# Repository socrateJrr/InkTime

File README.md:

# InkTime Smartwatch — PCB Design

InkTime este un smartwatch open-source si low-cost, cu ecran e-paper.

## Diagrama bloc

## BOM (Bill of Materials)

| Referinta    | Componenta               | Descriere                        | JLC Parts                                                                    | Datasheet                                                                                                   |
| ------------ | ------------------------ | -------------------------------- | ---------------------------------------------------------------------------- | ----------------------------------------------------------------------------------------------------------- |
| U1           | nRF52840-QIAA            | MCU principal BLE 5.0            | [JLC](https://jlcpcb.com/parts/componentSearch?searchTxt=nRF52840)           | [Datasheet](https://infocenter.nordicsemi.com/pdf/nRF52840_PS_v1.7.pdf)                                     |
| IC9          | RT6160AWSC               | DC/DC Buck-Boost 3.3V            | [JLC](https://jlcpcb.com/parts/componentSearch?searchTxt=RT6160AWSC)         | [Datasheet](https://www.richtek.com/assets/product_file/RT6160A/DS6160A-00.pdf)                             |
| IC1          | BQ25180YBGR              | LiPo Charger                     | [JLC](https://jlcpcb.com/parts/componentSearch?searchTxt=BQ25180)            | [Datasheet](https://www.ti.com/lit/ds/symlink/bq25180.pdf)                                                  |
| U3           | MAX17048G+T10            | Fuel Gauge I2C                   | [JLC](https://jlcpcb.com/parts/componentSearch?searchTxt=MAX17048G)          | [Datasheet](https://datasheets.maximintegrated.com/en/ds/MAX17048-MAX17049.pdf)                             |
| IC3          | BMA421                   | IMU Accelerometru 3 axe          | [JLC](https://jlcpcb.com/parts/componentSearch?searchTxt=BMA421)             | [Datasheet](https://www.bosch-sensortec.com/media/boschsensortec/downloads/datasheets/bst-bma421-ds000.pdf) |
| IC2          | DRV2605YZFR              | Haptic Driver I2C                | [JLC](https://jlcpcb.com/parts/componentSearch?searchTxt=DRV2605)            | [Datasheet](https://www.ti.com/lit/ds/symlink/drv2605.pdf)                                                  |
| ANT1         | 2450AT18B100E            | Antena Bluetooth 2.4GHz          | [JLC](https://jlcpcb.com/parts/componentSearch?searchTxt=2450AT18B100E)      | [Datasheet](https://www.johansontechnology.com/datasheets/2450AT18B100E/2450AT18B100E.pdf)                  |
| J1           | 503480-2400              | Conector display e-paper 24 pini | [JLC](https://jlcpcb.com/parts/componentSearch?searchTxt=503480-2400)        | [Datasheet](https://www.molex.com/pdm_docs/sd/5034802400_sd.pdf)                                            |
| J4           | KH-TYPE-C-16P            | Conector USB-C 16 pini           | [JLC](https://jlcpcb.com/parts/componentSearch?searchTxt=KH-TYPE-C-16P)      | -                                                                                                           |
| D3           | USBLC6-2SC6Y             | Protectie ESD USB                | [JLC](https://jlcpcb.com/parts/componentSearch?searchTxt=USBLC6-2SC6Y)       | [Datasheet](https://www.st.com/resource/en/datasheet/usblc6-2.pdf)                                          |
| D2, D4, D5   | MBR0530                  | Dioda Schottky                   | [JLC](https://jlcpcb.com/parts/componentSearch?searchTxt=MBR0530)            | [Datasheet](https://www.onsemi.com/pdf/datasheet/mbr0530-d.pdf)                                             |
| J2           | TC2030-IDC               | Conector SWD Tag-Connect         | [JLC](https://jlcpcb.com/parts/componentSearch?searchTxt=TC2030)             | [Datasheet](https://www.tag-connect.com/wp-content/uploads/bsk-pdf-manager/TC2030-IDC_1.pdf)                |
| X1           | Crystal 32MHz            | Cristal principal MCU            | [JLC](https://jlcpcb.com/parts/componentSearch?searchTxt=32MHz+crystal+3225) | -                                                                                                           |
| X2           | Crystal 32.768kHz        | Cristal RTC                      | [JLC](https://jlcpcb.com/parts/componentSearch?searchTxt=32768+crystal)      | -                                                                                                           |
| L7           | FTC252012SR47MBCA        | Inductor 0.47uH DC/DC            | [JLC](https://jlcpcb.com/parts/componentSearch?searchTxt=FTC252012SR47)      | -                                                                                                           |
| L5           | Inductor 68uH            | Inductor e-paper drive           | [JLC](https://jlcpcb.com/parts/componentSearch?searchTxt=68uH+inductor)      | -                                                                                                           |
| L1           | Inductor 3.9nH           | Inductor RF matching             | [JLC](https://jlcpcb.com/parts/componentSearch?searchTxt=3.9nH+inductor)     | -                                                                                                           |
| L2           | Inductor 15nH            | Inductor RF                      | [JLC](https://jlcpcb.com/parts/componentSearch?searchTxt=15nH+inductor)      | -                                                                                                           |
| L3           | Inductor 10uH            | Inductor DC/DC                   | [JLC](https://jlcpcb.com/parts/componentSearch?searchTxt=10uH+inductor+0402) | -                                                                                                           |
| Q1           | DMG2305UX-7              | MOSFET P-channel e-paper         | [JLC](https://jlcpcb.com/parts/componentSearch?searchTxt=DMG2305UX)          | [Datasheet](https://www.diodes.com/assets/Datasheets/DMG2305UX.pdf)                                         |
| Q3           | SI1308EDL-T1-GE3         | MOSFET N-channel e-paper         | [JLC](https://jlcpcb.com/parts/componentSearch?searchTxt=SI1308EDL)          | [Datasheet](https://www.vishay.com/docs/71509/si1308edl.pdf)                                                |
| SW_UP/DN/ENT | Butoane tactile SMD      | 3 butoane fizice                 | [JLC](https://jlcpcb.com/parts/componentSearch?searchTxt=tactile+button+smd) | -                                                                                                           |
| R*, C*       | Rezistente/Condensatoare | Diverse valori pasive            | [JLC](https://jlcpcb.com/parts)                                              | -                                                                                                           |

---

## Descrierea functionalitatii hardware

### Microcontroller — nRF52840 (U1)

Nucleul dispozitivului este **nRF52840** de la Nordic Semiconductor, un SoC cu procesor ARM Cortex-M4 la 64MHz si BLE 5.0 integrat. Acesta coordoneaza toate perifericele prin interfetele SPI, I2C si GPIO.

Antena externa **ANT1** (2450AT18B100E) este o antena ceramica de 2.4GHz plasata la marginea dreapta a placii. Sub antena exista un decupaj in PCB pentru a maximiza performanta RF — FR4-ul absoarbe semnalul daca antena sta direct pe el. Circuitul de adaptare RF include inductorii L1 (3.9nH), L2 (15nH) si condensatoarele C3, C4, C22.

**Interfete folosite:**

- **SPI** → display e-paper (J1): MOSI, SCK, CS, DC, RST, BUSY
- **I2C** → IMU (IC3), charger (IC1), haptic (IC2), fuel gauge (U3), DC/DC (IC9)
- **USB** → D+/D- prin protectie ESD D3
- **SWD** → programare/debug prin J2 (TC2030-IDC)
- **GPIO** → butoane, intreruperi IMU, HAPTIC_EN

### Alimentare

**IC1 (BQ25180YBGR)** — charger LiPo care preia alimentarea de la USB-C si incarca bateria. Comunica cu MCU prin I2C pentru statusul incarcarii.

**IC9 (RT6160AWSC)** — DC/DC buck-boost converter care genereaza **3.3V stabil** din tensiunea bateriei (3V–4.2V). Inductorul L7 (0.47uH) face parte din circuitul de comutare. Condensatoarele C23, C24 filtreaza intrarea si C25, C33 iesirea.

**U3 (MAX17048G+T10)** — fuel gauge care monitorizeaza nivelul bateriei prin I2C si trimite o intrerupere (ALERT) la nRF cand bateria scade sub un prag configurat.

Bateria se conecteaza direct la test pad-urile **TP_VBAT** si **TP_BAT_GND** (fara conector JST) pentru economisire de spatiu.

### Display e-paper — J1 (503480-2400)

Conector FFC ZIF cu 24 de pini. Circuitul de drive include Q3, Q1, L5 (68uH), D2, D4, D5 si condensatoarele EPD_C1...C12. Comunicatie prin **SPI** + GPIO de control.

### IMU — BMA421 (IC3)

Accelerometru triaxial Bosch conectat prin **I2C**. Folosit pentru wake-on-wrist, pedometru si detectie orientare. Intreruperile IMU_INT1/INT2 sunt conectate la GPIO-uri dedicate ale nRF.

### Haptic — DRV2605YZFR (IC2)

Driver de motor haptic controlat prin **I2C**, activat prin **HAPTIC_EN**. Suporta efecte LRA si ERM din biblioteca interna de 123 efecte.

### USB-C — KH-TYPE-C-16P (J4)

Conector USB-C cu protectie ESD asigurata de D3 (USBLC6-2SC6Y). R1_USB si R2_USB (5K1) pe pinii CC1/CC2 pentru detectia cablului USB.

### Programare SWD — TC2030-IDC (J2)

Conector Tag-Connect 6 pini pentru programare si debug SWD. Semnale: SWDIO, SWDCLK, RESET, SWO, 3.3V, GND.

---

## Pinii nRF52840 folositi

| Pin nRF52840  | Semnal    | Componenta             | Functie                       |
| ------------- | --------- | ---------------------- | ----------------------------- |
| P0.00 (XL1)   | XL1       | X1 (32MHz)             | Cristal principal — clock MCU |
| P0.01 (XL2)   | XL2       | X1 (32MHz)             | Cristal principal — clock MCU |
| P0.26         | SCL       | IC3, IC1, IC2, U3, IC9 | I2C clock                     |
| P0.27         | SDA       | IC3, IC1, IC2, U3, IC9 | I2C data                      |
| P0.13         | D-        | J4 via D3              | USB Data minus                |
| P0.14         | D+        | J4 via D3              | USB Data plus                 |
| P0.17         | EPD_RST   | J1                     | Reset display e-paper         |
| P0.18 (RESET) | RESET     | J2                     | Reset MCU via SWD             |
| P0.19         | EPD_BUSY  | J1                     | Status display e-paper        |
| P0.20         | EPD_DC    | J1                     | Data/Command display          |
| P0.21         | EPD_CS    | J1                     | Chip select display SPI       |
| P0.22         | SCK       | J1                     | SPI clock display             |
| P0.23         | MOSI      | J1                     | SPI data display              |
| P0.24         | SWDCLK    | J2                     | SWD clock programare          |
| P0.25         | SWDIO     | J2                     | SWD data programare           |
| P1.01         | HAPTIC_EN | IC2                    | Enable haptic driver          |
| P1.02         | PMIC_INT  | IC1                    | Intrerupere charger           |
| P1.03         | IMU_INT1  | IC3                    | Intrerupere IMU 1             |
| P1.04         | IMU_INT2  | IC3                    | Intrerupere IMU 2             |
| P1.05         | SW_UP     | SW_UP                  | Buton sus                     |
| P1.06         | SW_ENT    | SW_ENT                 | Buton enter                   |
| P1.07         | SW_DN     | SW_DN                  | Buton jos                     |
| ANT           | RF        | ANT1                   | Antena Bluetooth 2.4GHz       |
| VBUS          | VBUS      | J4                     | Detectie USB conectat         |
| DEC3V3        | 3V3       | IC9 output             | Alimentare 3.3V               |

---

## Structura PCB

**Dimensiuni:** 46mm x 35mm, grosime 1mm
**Straturi:** 4 (Top + GND + Power + Bottom)

| Strat            | Continut                        | Latime trasee |
| ---------------- | ------------------------------- | ------------- |
| Top              | Componente SMD + semnale date   | min 0.15mm    |
| GND (interior)   | Plan de masa complet            | -             |
| Power (interior) | Trasee 3V3, VBAT, VBUS, VREG    | 0.3mm         |
| Bottom           | Semnale suplimentare + plan GND | min 0.15mm    |

Toate componentele sunt plasate exclusiv pe stratul **TOP**.

---

## Decizii de design

**Alegerea 4 straturi**
S-a optat pentru 4 straturi datorita densitatii mari de componente si numarului mare de semnale. Stratul interior Power permite rutarea traseelor de alimentare (3V3, VBAT, VBUS) separat de semnale.

**Conectarea GND prin Copper Pour**
Pinii de GND nu au fost conectati manual prin trasee individuale.
In schimb, s-au realizat planuri de masa (copper pour GND) pe straturile
Top, GND interior si Bottom. Prin refill-ul poligoanelor, toate padurile
de GND se conecteaza automat la planul de cupru, eliminand necesitatea
airwires-urilor individuale de GND.

## Erori DRC acceptate

- **Board Outline Clearance (~40 erori)** — cauzate de plasarea butoanelor si mufei USB conform specificatiilor mecanice. Neglijate conform enuntului proiectului.
- **"Only INPUT pins on NET ID"** — ignorata conform indicatiilor din enunt.
- **Erori de Dimension la butoane si USB** — neglijate conform enuntului.
- **Overlap-uri** — in anumite zone foarte aglomerate ale PCB-ului, rutarea semnalelor nu a putut evita complet apropierea de pinii vecini fara a intrerupe conexiunile necesare. S-a acceptat un numar mic de overlap-uri in aceste zone.
- **Fisierul `.fbrd` de referinta furnizat continea deja ~46 de erori DRC** din cauza formei si constructiei componentelor. Acestea nu au putut fi eliminate deoarece tin de geometria placii impuse.

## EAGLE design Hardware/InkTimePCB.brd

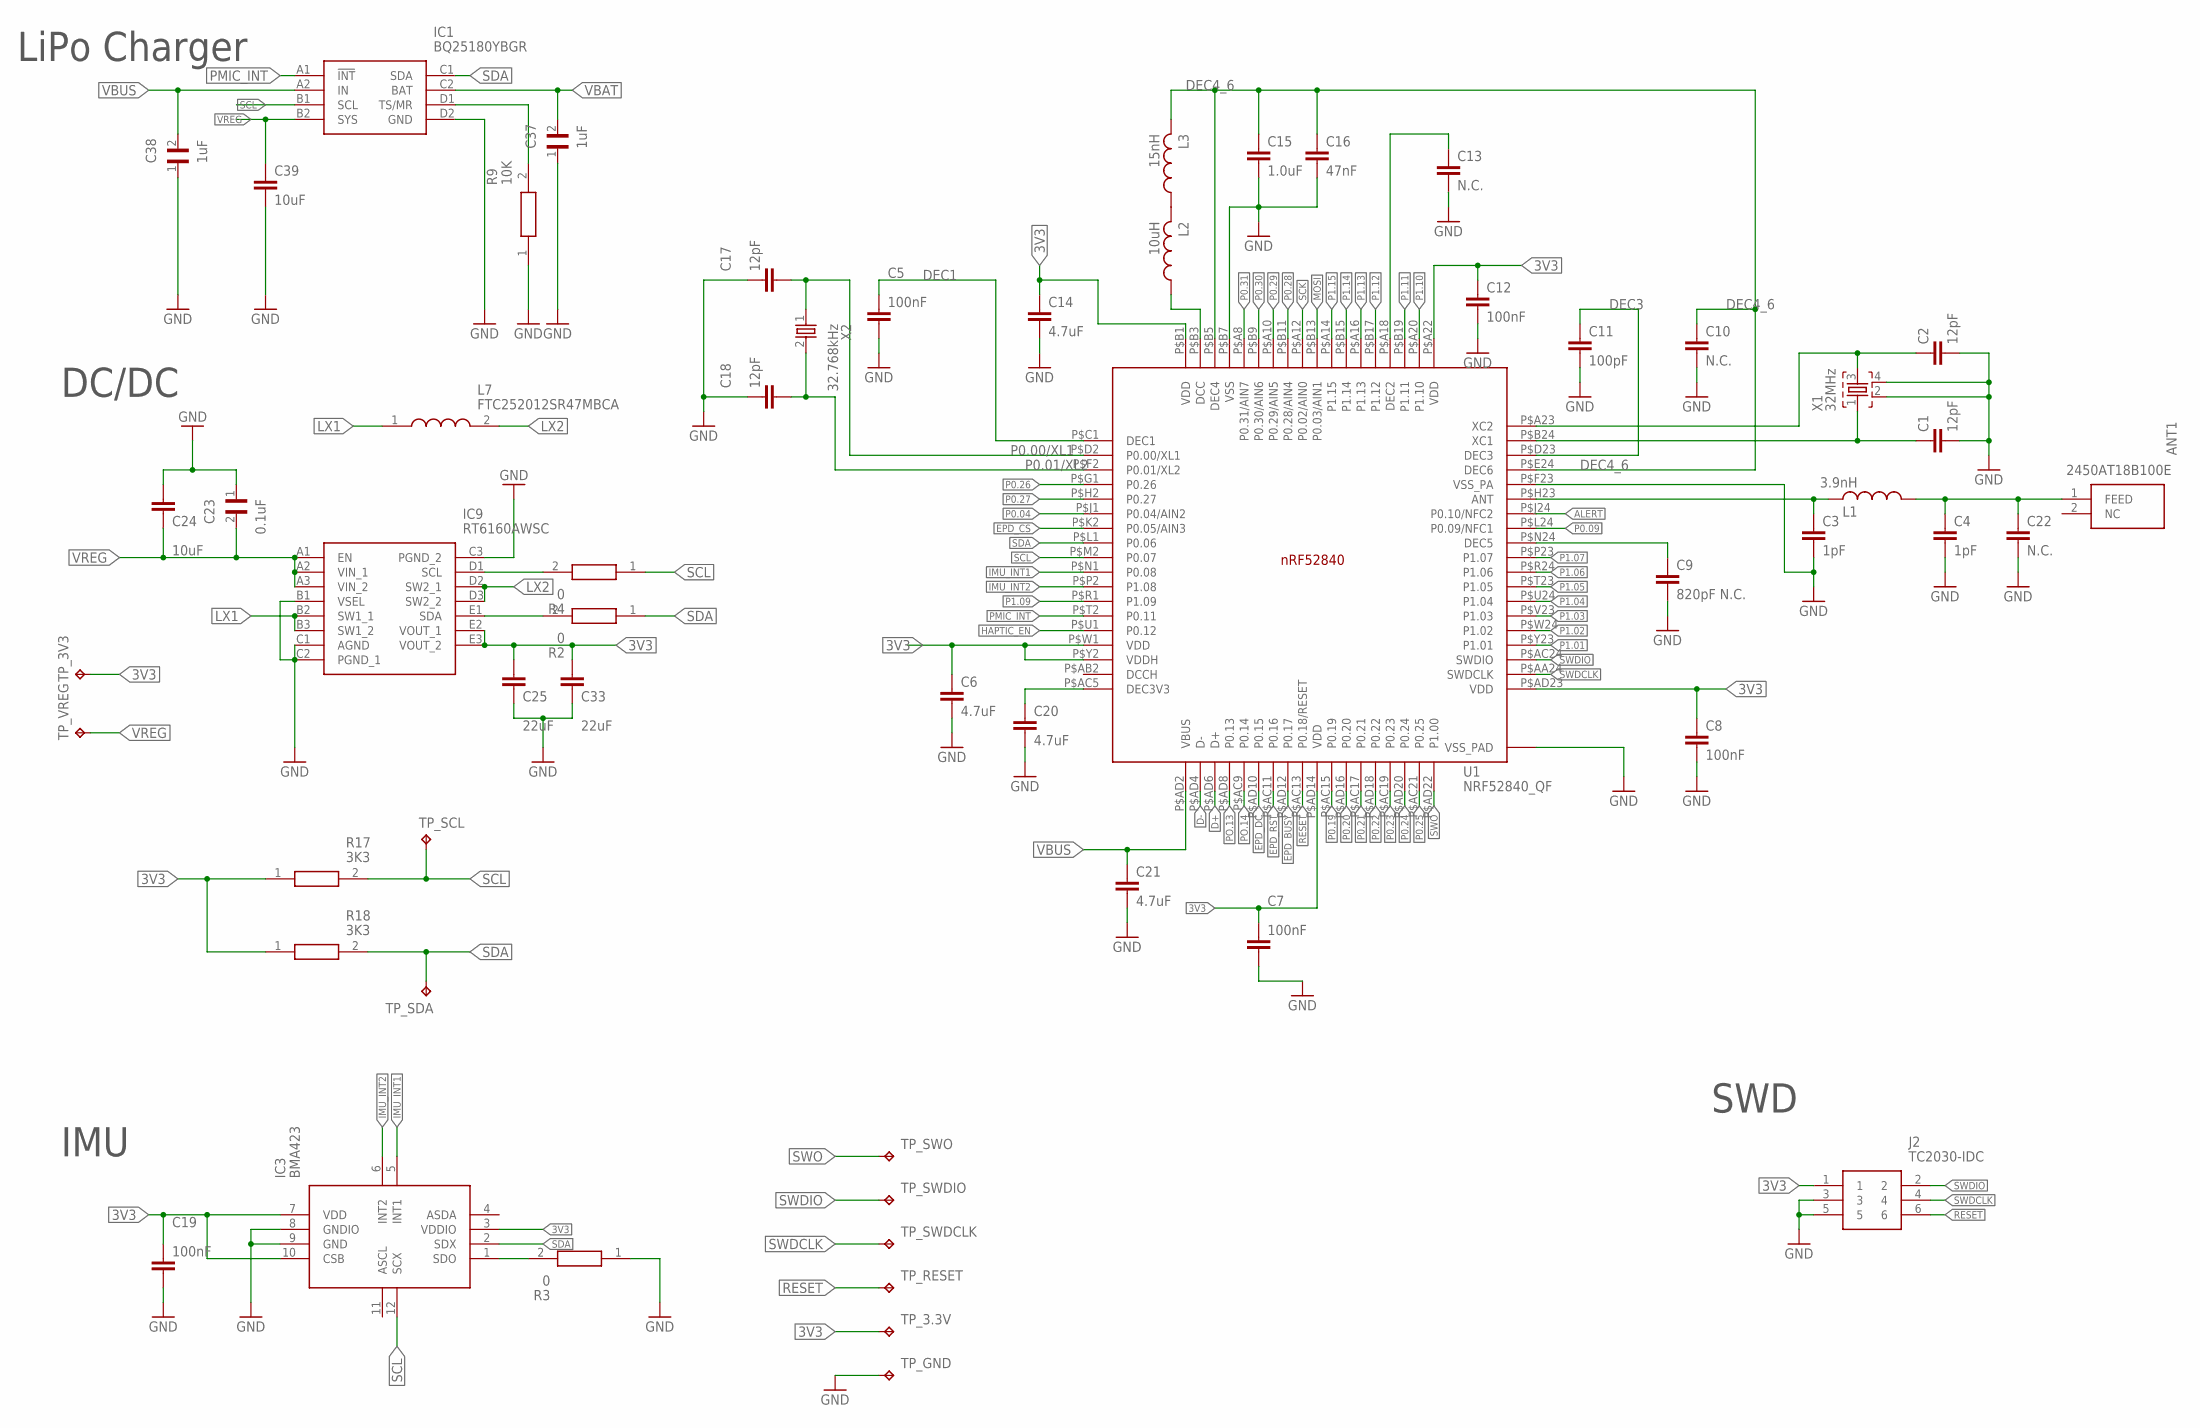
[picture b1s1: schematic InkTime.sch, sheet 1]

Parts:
ANT1: 2450AT18B100E; 2450AT18B100E_ANTC3216X140N
C1, C2, C17, C18: 12pF; NORDIC_NRF_3_RESC0201_L
C3, C4: 1pF; NORDIC_NRF_3_RESC0201_L
C5, C7, C8, C12, C19: 100nF; NORDIC_NRF_3_RESC0201_L
C6, C14, C20, C21: 4.7uF; PERFECT_0402_0402
C9: 820pF N.C.; NORDIC_NRF_3_RESC0201_L
C10, C13, C22: N.C.; NORDIC_NRF_3_RESC0201_L
C11: 100pF; NORDIC_NRF_3_RESC0201_L
C15: 1.0uF; PERFECT_0402_0402
C16: 47nF; NORDIC_NRF_3_RESC0201_L
C23: 0.1uF; GRM011R60J152KE01L_1_0201
C24: 10uF; PERFECT_0402_0402
C25, C33: 22uF; PERFECT_0402_0402
C37, C38: 1uF; GRM011R60J152KE01L_1_0201
C39: 10uF; ESP32_C6_LIBRARY_1_ESP32_WROVER_EAGLE-LTSPICE_C0402
IC1: BQ25180YBGR; BQ25180YBGR_BGA8C40P2X4_100X155X50
IC3: BMA423; BMA423_BMA423
IC9: RT6160AWSC; RT6160AWSC_BGA15C40P3X5_140X230X60
J2: TC2030-IDC; TC2030-IDC_TC2030IDC
L1: 3.9nH; NORDIC_NRF_2_RESC0402_L
L2: 10uH; NORDIC_NRF_2_RESC0402_L
L3: 15nH; NORDIC_NRF_2_RESC0402_L
L7: FTC252012SR47MBCA; MLP2016SR47MT0S1_INDC2016X100N
R2, R4: 0; ERA-1AEB3401C_0201
R3: 0; CPF0201D7K68C1_0201
R9: 10K; ERA-1AEB3401C_0201
R17, R18: 3K3; ERA-1AEB3401C_0201
TP_3.3V, TP_3V3: HECTOR_WATCH_1_TPTP20R; HECTOR_WATCH_1_TP20R
TP_GND: HECTOR_WATCH_1_TPTP20R; HECTOR_WATCH_1_TP20R
TP_RESET: HECTOR_WATCH_1_TPTP20R; HECTOR_WATCH_1_TP20R
TP_SCL: HECTOR_WATCH_1_TPTP20R; HECTOR_WATCH_1_TP20R
TP_SDA: HECTOR_WATCH_1_TPTP20R; HECTOR_WATCH_1_TP20R
TP_SWDCLK: HECTOR_WATCH_1_TPTP20R; HECTOR_WATCH_1_TP20R
TP_SWDIO: HECTOR_WATCH_1_TPTP20R; HECTOR_WATCH_1_TP20R
TP_SWO: HECTOR_WATCH_1_TPTP20R; HECTOR_WATCH_1_TP20R
TP_VREG: HECTOR_WATCH_1_TPTP20R; HECTOR_WATCH_1_TP20R
U1: NRF52840_QF; NORDIC_NRF_4_AQFN50P700X700X85_HS-74N
X1: 32MHz; NORDIC_NRF_BT-XTAL_2016_N
X2: 32.768kHz; NORDIC_NRF_1_XTAL_3215_N

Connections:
3V3: C6.1, C7.1, C8.1, C12.1, C14.1, C19.1, C25.1, C33.1, IC3.3 (VDDIO), IC3.7 (VDD), IC3.10 (CSB), IC9.E2 (VOUT_1), IC9.E3 (VOUT_2), J2.1, R17.1, R18.1, TP_3.3V.TP, TP_3V3.TP, U1.P$A22 (VDD), U1.P$AD14 (VDD), U1.P$AD23 (VDD), U1.P$B1 (VDD), U1.P$W1 (VDD), U1.P$Y2 (VDDH); also elsewhere on the board
ALERT: U1.P$J24 (P0.10/NFC2); also elsewhere on the board
D+: U1.P$AD6 (D+); also elsewhere on the board
D-: U1.P$AD4 (D-); also elsewhere on the board
DEC1: C5.1, U1.P$C1 (DEC1)
DEC3: C11.1, U1.P$D23 (DEC3)
DEC4_6: C10.1, C15.1, C16.1, L3.2, U1.P$B5 (DEC4), U1.P$E24 (DEC6)
EPD_BUSY: U1.P$AD12 (P0.17); also elsewhere on the board
EPD_CS: U1.P$K2 (P0.05/AIN3); also elsewhere on the board
EPD_DC: U1.P$AD10 (P0.15); also elsewhere on the board
EPD_RST: U1.P$AC11 (P0.16); also elsewhere on the board
GND: C1.2, C2.2, C3.2, C4.2, C5.2, C6.2, C7.2, C8.2, C9.2, C10.2, C11.2, C12.2, C13.2, C14.2, C15.2, C16.2, C17.1, C18.1, C19.2, C20.2, C21.2, C22.2, C23.1, C24.1, C25.2, C33.2, C37.1, C38.1, C39.2, IC1.D2 (GND), IC3.8 (GNDIO), IC3.9 (GND), IC9.B1 (VSEL), IC9.C1 (AGND), IC9.C2 (PGND_1), IC9.C3 (PGND_2), J2.3, J2.5, R3.1, R9.1, TP_GND.TP, U1.P$74 (VSS_PAD), U1.P$75 (VSS_PAD), U1.P$76 (VSS_PAD), U1.P$77 (VSS_PAD), U1.P$78 (VSS_PAD), U1.P$79 (VSS_PAD), U1.P$80 (VSS_PAD), U1.P$81 (VSS_PAD), U1.P$82 (VSS_PAD), U1.P$83 (VSS_PAD), U1.P$84 (VSS_PAD), U1.P$85 (VSS_PAD), U1.P$86 (VSS_PAD), U1.P$87 (VSS_PAD), U1.P$88 (VSS_PAD), U1.P$89 (VSS_PAD), U1.P$90 (VSS_PAD), U1.P$B7 (VSS), U1.P$F23 (VSS_PA), X1.2, X1.4; also elsewhere on the board
HAPTIC_EN: U1.P$U1 (P0.12); also elsewhere on the board
IMU_INT1: IC3.5 (INT1), U1.P$N1 (P0.08)
IMU_INT2: IC3.6 (INT2), U1.P$P2 (P1.08)
LX1: IC9.B2 (SW1_1), IC9.B3 (SW1_2), L7.1
LX2: IC9.D2 (SW2_1), IC9.D3 (SW2_2), L7.2
MOSI: U1.P$B13 (P0.03/AIN1); also elsewhere on the board
unnamed: ANT1.1 (FEED), C4.1, C22.1, L1.2
unnamed: IC9.D1 (SCL), R4.2
unnamed: IC1.D1 (TS/MR), R9.2
unnamed: C2.1, U1.P$A23 (XC2), X1.3
unnamed: IC9.E1 (SDA), R2.2
unnamed: L2.2, L3.1
unnamed: IC3.1 (SDO), R3.2
unnamed: C1.1, U1.P$B24 (XC1), X1.1
unnamed: C3.1, L1.1, U1.P$H23 (ANT)
unnamed: C9.1, U1.P$N24 (DEC5)
unnamed: C20.1, U1.P$AC5 (DEC3V3)
unnamed: L2.1, U1.P$B3 (DCC)
unnamed: C13.1, U1.P$A18 (DEC2)
P0.00/XL1: C17.2, U1.P$D2 (P0.00/XL1), X2.1
P0.01/XL2: C18.2, U1.P$F2 (P0.01/XL2), X2.2
P0.04: U1.P$J1 (P0.04/AIN2)
P0.09: U1.P$L24 (P0.09/NFC1)
P0.19: U1.P$AC15 (P0.19)
P0.20: U1.P$AD16 (P0.20)
P0.21: U1.P$AC17 (P0.21)
P0.22: U1.P$AD18 (P0.22)
P0.23: U1.P$AC19 (P0.23)
P0.24: U1.P$AD20 (P0.24)
P0.25: U1.P$AC21 (P0.25)
P0.26: U1.P$G1 (P0.26)
P0.27: U1.P$H2 (P0.27)
P0.28: U1.P$B11 (P0.28/AIN4)
P0.29: U1.P$A10 (P0.29/AIN5)
P0.30: U1.P$B9 (P0.30/AIN6)
P0.31: U1.P$A8 (P0.31/AIN7)
P1.01: U1.P$Y23 (P1.01); also elsewhere on the board
P1.02: U1.P$W24 (P1.02); also elsewhere on the board
P1.03: U1.P$V23 (P1.03)
P1.04: U1.P$U24 (P1.04)
P1.05: U1.P$T23 (P1.05)
P1.06: U1.P$R24 (P1.06)
P1.07: U1.P$P23 (P1.07)
P1.09: U1.P$R1 (P1.09)
P1.10: U1.P$A20 (P1.10)
P1.11: U1.P$B19 (P1.11)
P1.12: U1.P$B17 (P1.12)
P1.13: U1.P$A16 (P1.13)
P1.14: U1.P$B15 (P1.14)
P1.15: U1.P$A14 (P1.15)
PMIC_INT: IC1.A1 (!INT), U1.P$T2 (P0.11)
PO.13: U1.P$AD8 (P0.13)
PO.14: U1.P$AC9 (P0.14)
RESET: J2.6, TP_RESET.TP, U1.P$AC13 (P0.18/RESET)
SCK: U1.P$A12 (P0.02/AIN0); also elsewhere on the board
SCL: IC1.B1 (SCL), IC3.12 (SCX), R4.1, R17.2, TP_SCL.TP, U1.P$M2 (P0.07); also elsewhere on the board
SDA: IC1.C1 (SDA), IC3.2 (SDX), R2.1, R18.2, TP_SDA.TP, U1.P$L1 (P0.06); also elsewhere on the board
SWDCLK: J2.4, TP_SWDCLK.TP, U1.P$AA24 (SWDCLK)
SWDIO: J2.2, TP_SWDIO.TP, U1.P$AC24 (SWDIO)
SWO: TP_SWO.TP, U1.P$AD22 (P1.00)
VBAT: C37.2, IC1.C2 (BAT); also elsewhere on the board
VBUS: C21.1, C38.2, IC1.A2 (IN), U1.P$AD2 (VBUS); also elsewhere on the board
VREG: C23.2, C24.2, C39.1, IC1.B2 (SYS), IC9.A1 (EN), IC9.A2 (VIN_1), IC9.A3 (VIN_2), TP_VREG.TP

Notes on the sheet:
LiPo Charger
DC/DC
IMU
SWD

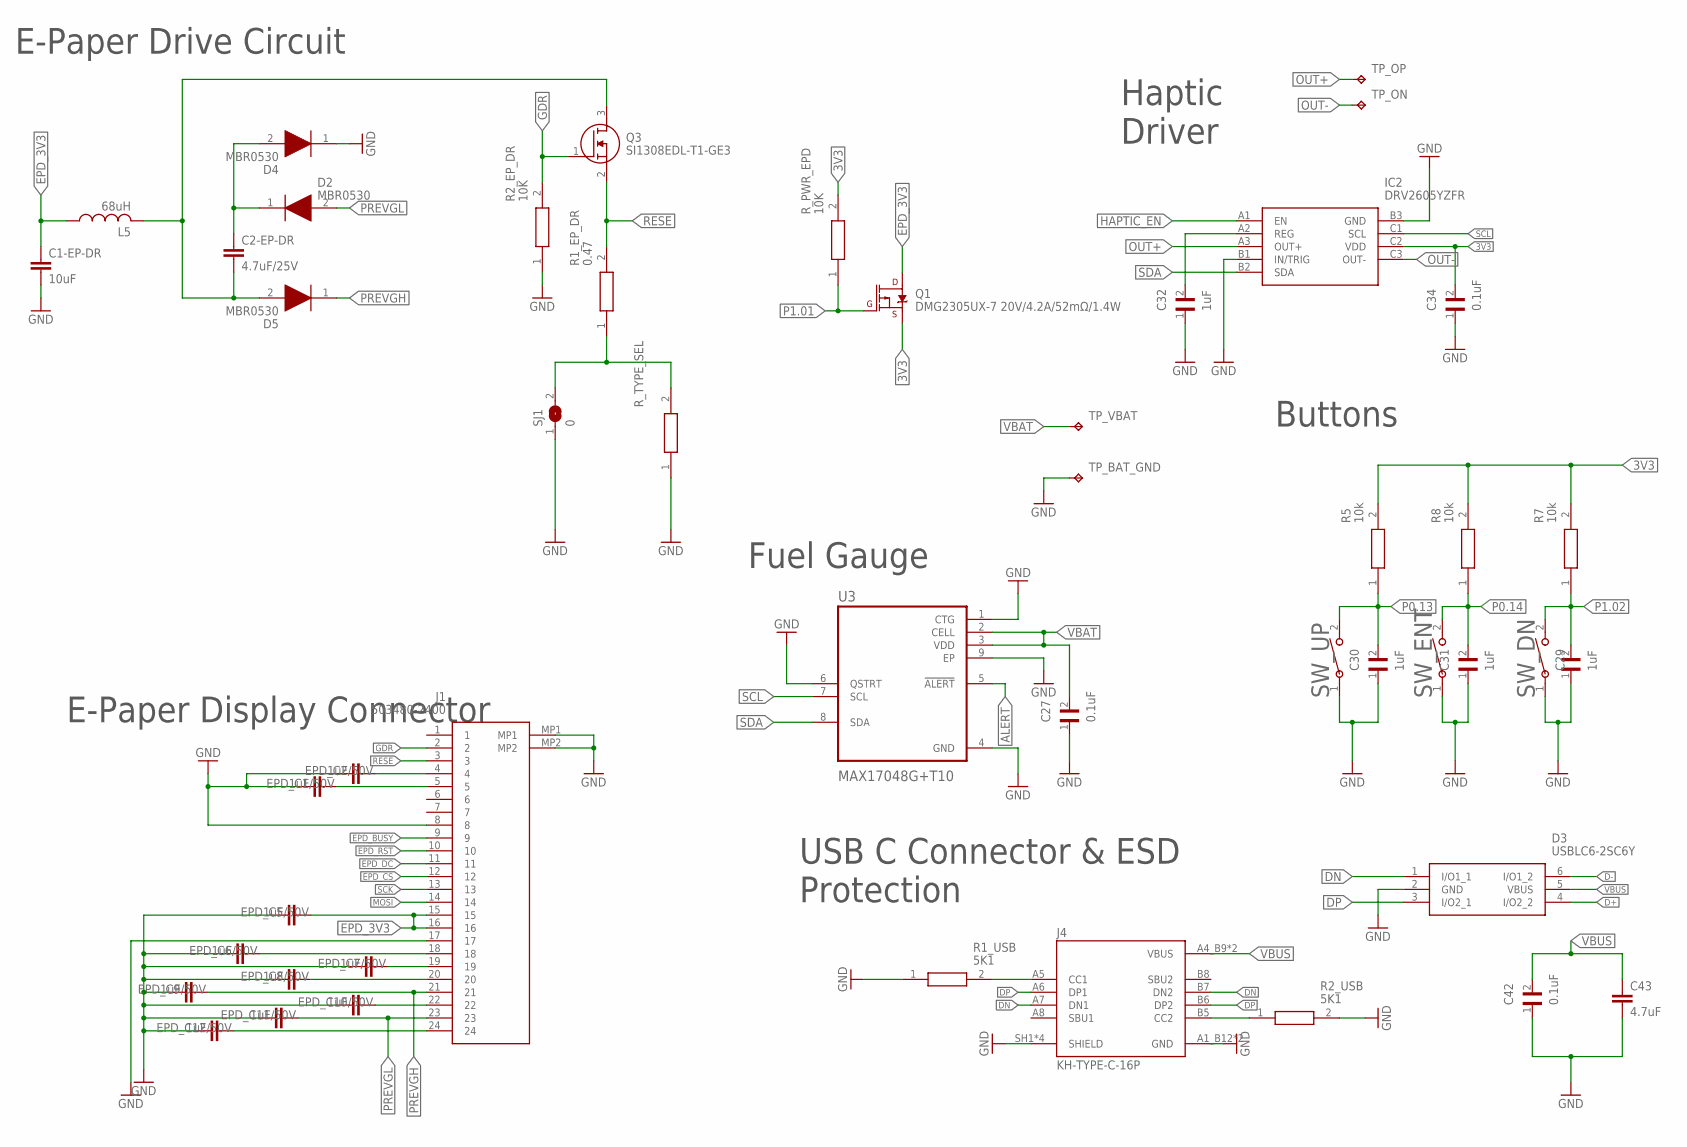
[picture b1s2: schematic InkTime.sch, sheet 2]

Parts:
C1-EP-DR: 10uF; PERFECT_0402_0402
C2-EP-DR: 4.7uF/25V; PERFECT_0402_0402
C27, C34, C42: 0.1uF; GRM011R60J152KE01L_2_CAPC0201X13N
C29, C30, C31, C32: 1uF; GRM011R60J152KE01L_2_CAPC0201X13N
C43: 4.7uF; PERFECT_0402_0402
D2, D4, D5: MBR0530; ESP32_C6_LIBRARY_5_SOD3716X135N
D3: USBLC6-2SC6Y; ESP32_C6_LIBRARY_3_SOT95P280X145-6N
EPD_C1, EPD_C2, EPD_C5, EPD_C6, EPD_C7, EPD_C8, EPD_C9, EPD_C10, EPD_C11, EPD_C12: 1uF/50V; PERFECT_0402_0402
IC2: DRV2605YZFR; DRV2605YZFR_BGA9C50P3X3_144X144X62
J1: 503480-2400; 503480-2400_5034802400
J4: KH-TYPE-C-16P; KH-TYPE-C-16P_KINGHELM_KH-TYPE-C-16P
L5: 68uH; NORDIC_NRF_2_RESC0402_L
Q1: DMG2305UX-7 20V/4.2A/52mΩ/1.4W; ESP32_C6_LIBRARY_4_ESP32_C6_LIBRARY_4_ESP32_C6_LIBRARY_4_ES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
Q3: SI1308EDL-T1-GE3; ESP32_C6_LIBRARY_6_SOT65P210X110-3N
R1_EP_DR: 0.47; ERA-1AEB3401C_0201
R1_USB, R2_USB: 5K1; CPF0201D7K68C1_0201
R2_EP_DR: 10K; ERA-1AEB3401C_0201
R5, R7, R8: 10k; CPF0201D7K68C1_0201
R_PWR_EPD: 10K; CPF0201D7K68C1_0201
R_TYPE_SEL: 2.2; ERA-1AEB3401C_0201
SJ1: 0; ESP32_C6_LIBRARY_7_JUMPER_SJ
SW_DN: 2025-10-22_07-23-44_LIBRARY_EVP-AKE31ASW_EVP-AKE3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; 2025-10-22_07-23-44_LIBRARY_SW_EVP-AKE31A_PAN
SW_ENT: 2025-10-22_07-23-44_LIBRARY_EVP-AKE31ASW_EVP-AKE3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; 2025-10-22_07-23-44_LIBRARY_SW_EVP-AKE31A_PAN
SW_UP: 2025-10-22_07-23-44_LIBRARY_EVP-AKE31ASW_EVP-AKE3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; 2025-10-22_07-23-44_LIBRARY_SW_EVP-AKE31A_PAN
TP_BAT_GND: HECTOR_WATCH_1_TPTP20R; HECTOR_WATCH_1_TP20R
TP_ON: HECTOR_WATCH_1_TPTP20R; HECTOR_WATCH_1_TP20R
TP_OP: HECTOR_WATCH_1_TPTP20R; HECTOR_WATCH_1_TP20R
TP_VBAT: HECTOR_WATCH_1_TPTP20R; HECTOR_WATCH_1_TP20R
U3: MAX17048G+T10; ESP32_C6_LIBRARY_SON50P200X200X80-9N

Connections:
3V3: C34.2, IC2.C2 (VDD), Q1.2 (S), R5.2, R7.2, R8.2, R_PWR_EPD.2; also elsewhere on the board
ALERT: U3.5 (!ALERT); also elsewhere on the board
D+: D3.4 (I/O2_2); also elsewhere on the board
D-: D3.6 (I/O1_2); also elsewhere on the board
DN: D3.1 (I/O1_1), J4.A7 (DN1), J4.B7 (DN2)
DP: D3.3 (I/O2_1), J4.A6 (DP1), J4.B6 (DP2)
EPD_3V3: C1-EP-DR.1, EPD_C5.2, J1.15, J1.16, L5.1, Q1.3 (D)
EPD_BUSY: J1.9; also elsewhere on the board
EPD_CS: J1.12; also elsewhere on the board
EPD_DC: J1.11; also elsewhere on the board
EPD_RST: J1.10; also elsewhere on the board
GDR: J1.2, Q3.1 (G), R2_EP_DR.2
GND: C1-EP-DR.2, C27.1, C29.1, C30.1, C31.1, C32.1, C34.1, C42.1, C43.2, D3.2 (GND), D4.1 (K), EPD_C1.1, EPD_C2.1, EPD_C5.1, EPD_C6.1, EPD_C7.1, EPD_C8.1, EPD_C9.1, EPD_C10.1, EPD_C11.1, EPD_C12.1, IC2.B1 (IN/TRIG), IC2.B3 (GND), J1.8, J1.17, J1.MP1, J1.MP2, J4.A1_B12 (GND), J4.A12_B1 (GND), J4.SH1 (SHIELD), J4.SH2 (SHIELD), J4.SH3 (SHIELD), J4.SH4 (SHIELD), R1_USB.1, R2_EP_DR.1, R2_USB.2, R_TYPE_SEL.1, SJ1.1, SW_DN.1, SW_ENT.1, SW_UP.1, TP_BAT_GND.TP, U3.1 (CTG), U3.4 (GND), U3.6 (QSTRT), U3.9 (EP); also elsewhere on the board
HAPTIC_EN: IC2.A1 (EN); also elsewhere on the board
MOSI: J1.14; also elsewhere on the board
unnamed: J4.A5 (CC1), R1_USB.2
unnamed: C32.2, IC2.A2 (REG)
unnamed: C2-EP-DR.1, D2.1 (K), D4.2 (A)
unnamed: R1_EP_DR.1, R_TYPE_SEL.2, SJ1.2
unnamed: C2-EP-DR.2, D5.2 (A), L5.2, Q3.3 (D)
unnamed: EPD_C2.2, J1.4
unnamed: EPD_C1.2, J1.5
unnamed: J4.B5 (CC2), R2_USB.1
unnamed: EPD_C6.2, J1.18
unnamed: EPD_C7.2, J1.19
unnamed: EPD_C8.2, J1.20
unnamed: EPD_C10.2, J1.22
unnamed: EPD_C12.2, J1.24
OUT+: IC2.A3 (OUT+), TP_OP.TP
OUT-: IC2.C3 (OUT-), TP_ON.TP
P0.13: C30.2, R5.1, SW_UP.2
P0.14: C31.2, R8.1, SW_ENT.2
P1.01: Q1.1 (G), R_PWR_EPD.1; also elsewhere on the board
P1.02: C29.2, R7.1, SW_DN.2; also elsewhere on the board
PREVGH: D5.1 (K), EPD_C9.2, J1.21
PREVGL: D2.2 (A), EPD_C11.2, J1.23
RESE: J1.3, Q3.2 (S), R1_EP_DR.2
SCK: J1.13; also elsewhere on the board
SCL: IC2.C1 (SCL), U3.7 (SCL); also elsewhere on the board
SDA: IC2.B2 (SDA), U3.8 (SDA); also elsewhere on the board
VBAT: C27.2, TP_VBAT.TP, U3.2 (CELL), U3.3 (VDD); also elsewhere on the board
VBUS: C42.2, C43.1, D3.5 (VBUS), J4.A4_B9 (VBUS), J4.A9_B4 (VBUS); also elsewhere on the board

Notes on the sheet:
E-Paper Drive Circuit
E-Paper Display Connector
Fuel Gauge
Haptic Driver
Buttons
USB C Connector & ESD Protection

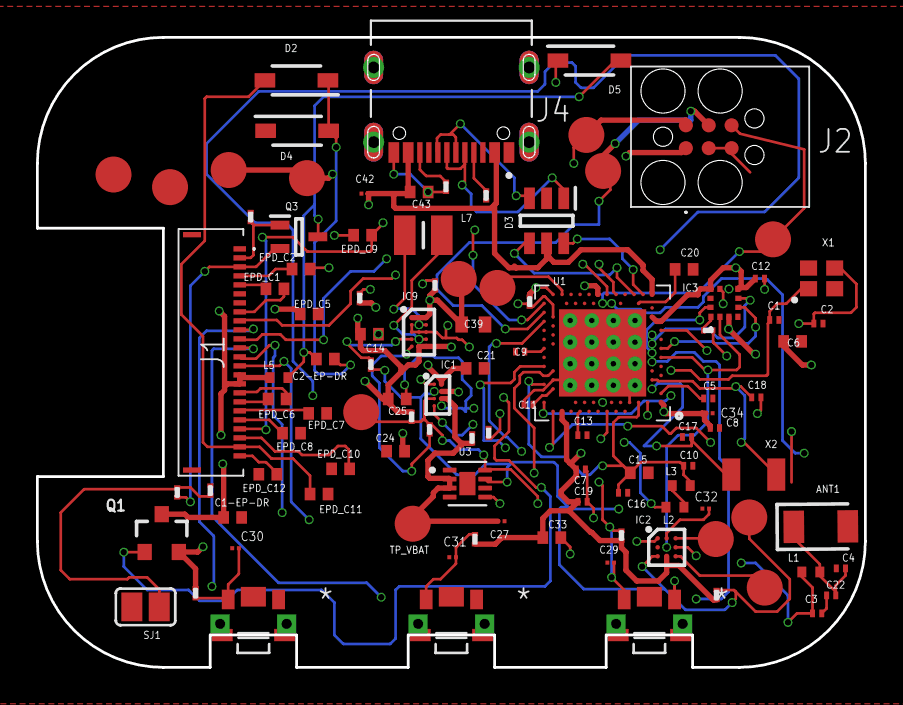
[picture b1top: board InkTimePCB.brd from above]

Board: 4 copper layers, 46.0 x 35.0 mm, 105 parts (0 on the bottom side), 70 nets.

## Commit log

2026-04-10 Add files via upload
    first commit
2026-04-10 Add files via upload
    am incarcat si separat fiecare file
2026-04-10 Add README for InkTime smartwatch project
    Added project description and specifications for InkTime smartwatch PCB design.
2026-04-10 Rename InkTime.fsch to Hardware/InkTime.fsch
2026-04-10 Rename InkTimePCB.fbrd to Hardware/InkTimePCB.fbrd
2026-04-10 Rename InkTimePCB3_LETS.f3d to Images/InkTimePCB3_LETS.f3d
2026-04-10 Rename inkTime_project.f3z to Manufacturing/inkTime_project.f3z
2026-04-10 Rename Screenshot 2026-04-10 221149.png to Mechanical/Screenshot 2026-04-10 221149.png
2026-04-20 Revise InkTime smartwatch project documentation
    Updated README.md to enhance project description and details.
2026-04-20 Rename InkTime.pdf to Hardware/InkTime.pdf
2026-04-20 Rename assembly.cpl to cpl.cpl
2026-04-20 Add exploded view STEP file
2026-04-20 Create LICENSE
2026-04-22 Add InkTime exploded view

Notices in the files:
parts and their libraries:
InkTime_v5: COPYRIGHT: Copyright (C) 2025 Ultra Librarian. All rights reserved.
